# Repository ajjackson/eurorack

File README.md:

# ajjackson's DIY synth stuff

Somewhere to capture and develop some ideas for novel synthesiser
modules. Currently that means Eurorack, so +/- 12V power, TS mini
jacks, 10V peak-to-peak audio signals.

Not clear at this stage if the end goal is perfboard or PCBs, will see
how ambitious the designs get...

License is CC-by-sa where appropriate

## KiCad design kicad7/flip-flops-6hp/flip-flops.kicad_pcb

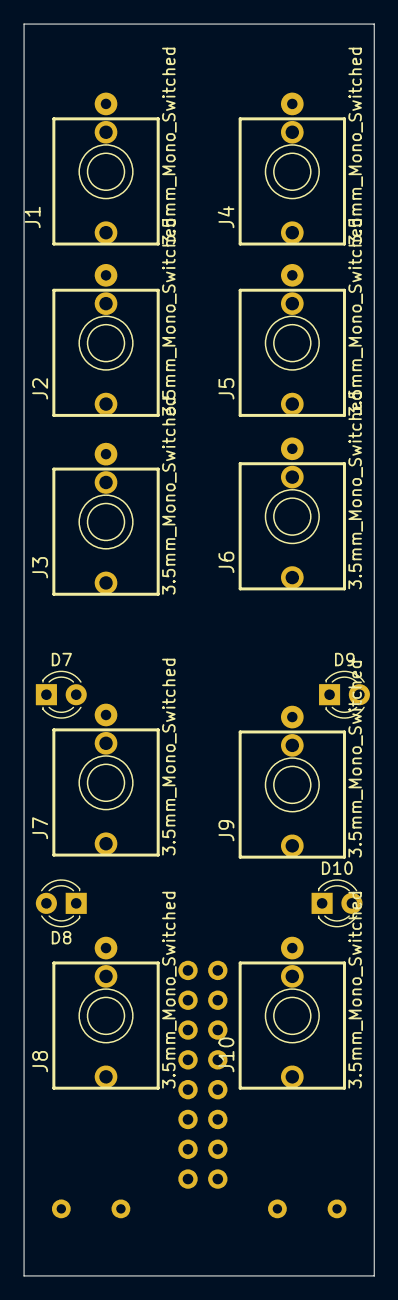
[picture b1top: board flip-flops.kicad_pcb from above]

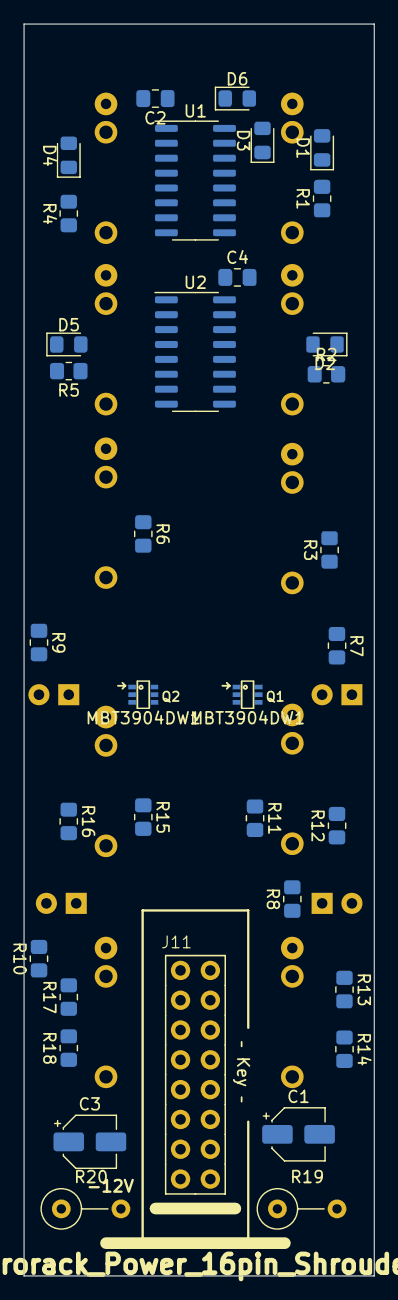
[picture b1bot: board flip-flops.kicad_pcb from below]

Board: 2 copper layers, 29.8 x 106.7 mm, 49 parts (35 on the bottom side), 39 nets, no tracks yet.

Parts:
C1, C3: 10uF_4x5.3_10V; CP_Elec_4x5.3
C2, C4: 100n; C_0805_2012Metric_Pad1.18x1.45mm_HandSolder
D1, D2, D3, D4, D5, D6: D_Schottky; D_0805_2012Metric_Pad1.15x1.40mm_HandSolder
D7, D8, D9, D10: LED; LED_D3.0mm_FlatTop
J1, J2, J3, J4, J5, J6, J7, J8, J9, J10: 3.5mm_Mono_Switched; EighthInch_PJ398SM
J11: Eurorack_Power_16pin_Shrouded; Pins_2x08_2.54mm_TH_EuroPower_Shrouded
Q1, Q2: MBT3904DW1; SOT-363_SC-70-6
R1, R2, R3, R4, R5, R6: 100k; R_0805_2012Metric_Pad1.20x1.40mm_HandSolder
R7, R8, R9, R10, R11, R12, R13, R14, R15, R16, R17, R18: 2.2k; R_0805_2012Metric_Pad1.20x1.40mm_HandSolder
R19, R20: 10R; R_Axial_DIN0309_L9.0mm_D3.2mm_P5.08mm_Vertical
U1: 4050; SOIC-16_3.9x9.9mm_P1.27mm
U2: 4013; SOIC-16_3.9x9.9mm_P1.27mm

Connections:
+5V: C2.1, C3.1, C4.1, R20.2, U1.1 (VCC), U2.14 (VDD)
+12V: C1.1, Q1.3 (C2), Q1.6 (C1), Q2.3 (C2), Q2.6 (C1), R19.1
/INV_OUT_1: J1.3 (SW), J8.1 (SIG), R13.2, R14.1
/INV_OUT_2: J4.3 (SW), J10.1 (SIG), R17.2, R18.1
GND: C1.2, C2.2, C3.2, C4.2, D1.2 (A), D2.2 (A), D3.2 (A), D4.2 (A), D5.2 (A), D6.2 (A), D7.1 (K), D8.1 (K), D9.1 (K), D10.1 (K), J1.2 (SHEILD), J2.2 (SHEILD), J3.2 (SHEILD), J3.3 (SW), J4.2 (SHEILD), J5.2 (SHEILD), J6.2 (SHEILD), J7.2 (SHEILD), J8.2 (SHEILD), J9.2 (SHEILD), J10.2 (SHEILD), J11.9 (GND), J11.10 (GND), J11.11 (GND), J11.12 (GND), J11.13 (-12), J11.14 (-12V), R12.2, R14.2, R16.2, R18.2, U1.8 (VSS), U2.7 (VSS)
unnamed: D1.1 (K), R1.2, U1.9
unnamed: D2.1 (K), R2.2, U1.11
unnamed: D3.1 (K), R3.2, U1.14
unnamed: D4.1 (K), R4.2, U1.3
unnamed: D5.1 (K), R5.2, U1.5
unnamed: D6.1 (K), R6.2, U1.7
unnamed: D7.2 (A), R7.2
unnamed: D8.2 (A), R8.2
unnamed: D9.2 (A), R9.2
unnamed: D10.2 (A), R10.2
unnamed: J1.1 (SIG), R1.1
unnamed: J2.1 (SIG), R2.1
unnamed: J3.1 (SIG), R3.1
unnamed: J4.1 (SIG), R4.1
unnamed: J5.1 (SIG), R5.1
unnamed: J6.1 (SIG), R6.1
unnamed: J7.1 (SIG), R11.2, R12.1
unnamed: J9.1 (SIG), R15.2, R16.1
unnamed: J11.7 (12V), J11.8 (+12V), R19.2
unnamed: J11.5 (+12V), J11.6, R20.1
unnamed: Q1.2 (B1), U2.13 (Q)
unnamed: Q1.1 (E1), R7.1, R11.1
unnamed: Q1.5 (B2), U2.12 (~Q)
unnamed: Q1.4 (E2), R8.1, R13.1
unnamed: Q2.2 (B1), U2.1 (Q)
unnamed: Q2.1 (E1), R9.1, R15.1
unnamed: Q2.5 (B2), U2.2 (~Q)
unnamed: Q2.4 (E2), R10.1, R17.1
unnamed: U1.4, U2.3 (C)
unnamed: U1.2, U2.5 (D)
unnamed: U1.6, U2.4 (R)
unnamed: U1.12, U2.11 (C)
unnamed: U1.10, U2.9 (D)
unnamed: U1.15, U2.10 (R)

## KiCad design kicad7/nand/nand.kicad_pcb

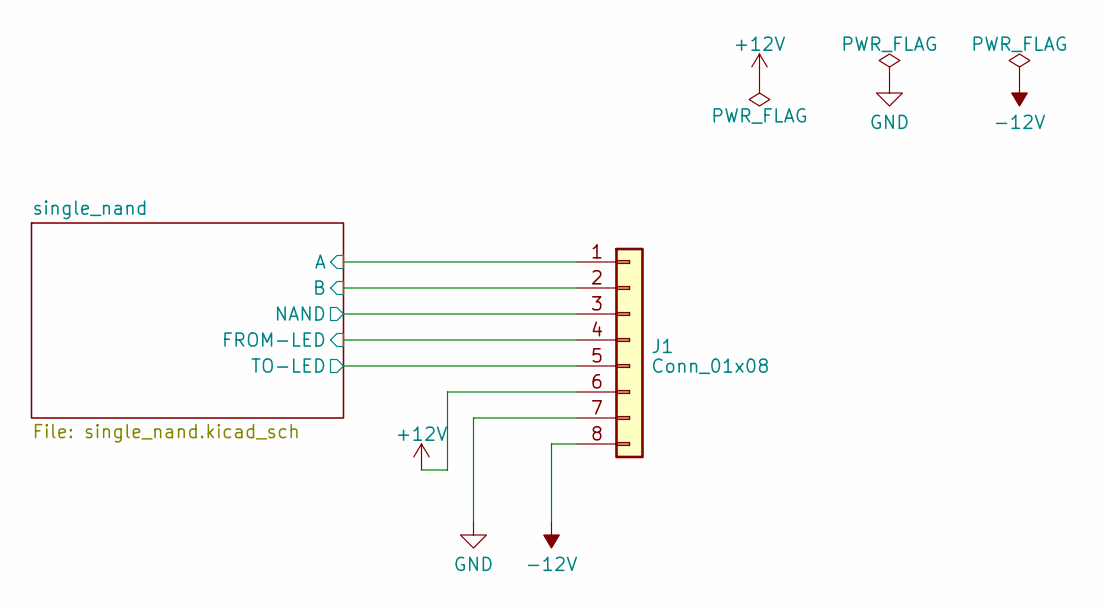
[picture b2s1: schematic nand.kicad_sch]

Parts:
J1: Conn_01x08; PinHeader_1x08_P2.54mm_Horizontal

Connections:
+12V: J1.6; also elsewhere on the board
-12V: J1.8; also elsewhere on the board
/single_nand/A: J1.1; also elsewhere on the board
/single_nand/B: J1.2; also elsewhere on the board
/single_nand/FROM-LED: J1.4; also elsewhere on the board
/single_nand/NAND: J1.3; also elsewhere on the board
/single_nand/TO-LED: J1.5; also elsewhere on the board
GND: J1.7; also elsewhere on the board

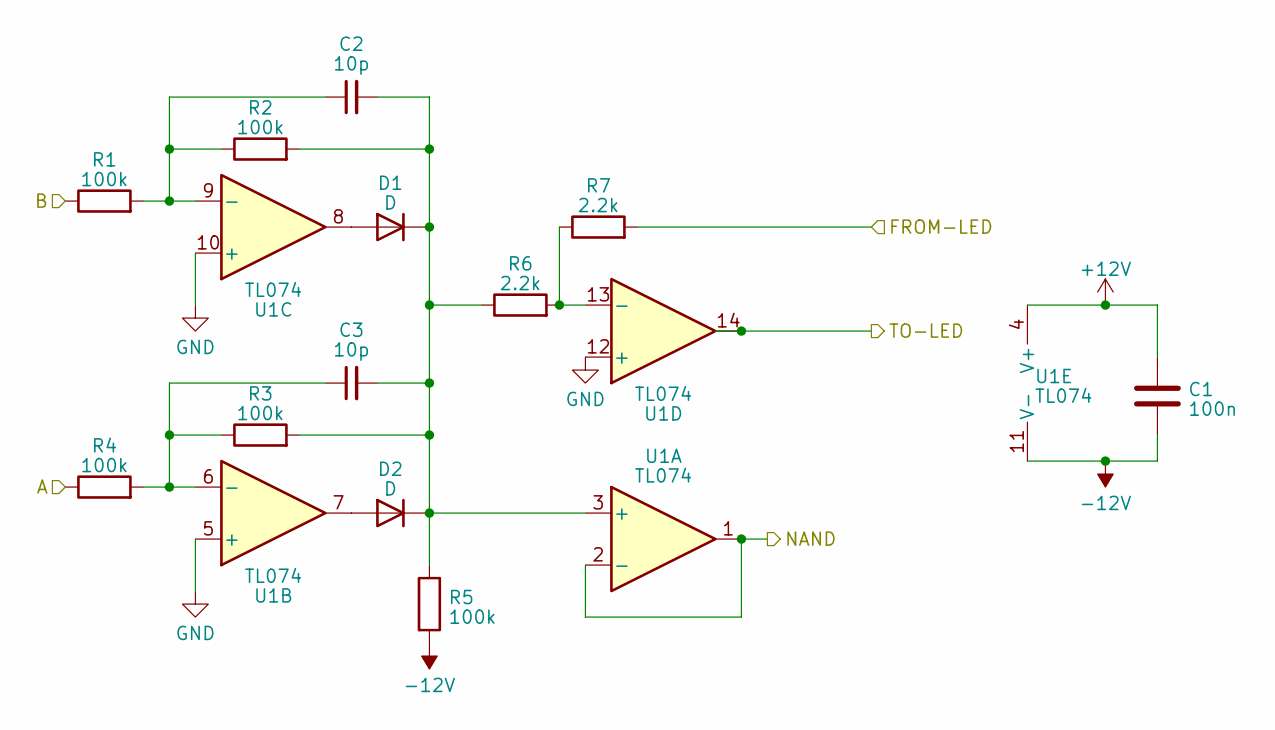
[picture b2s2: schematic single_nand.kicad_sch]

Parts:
C1: 100n; C_Disc_D5.0mm_W2.5mm_P5.00mm
C2, C3: 10p; C_Disc_D5.0mm_W2.5mm_P5.00mm
D1, D2: D; D_DO-34_SOD68_P7.62mm_Horizontal
R1, R2, R3, R4, R5: 100k; R_Axial_DIN0207_L6.3mm_D2.5mm_P7.62mm_Horizontal
R6, R7: 2.2k; R_Axial_DIN0207_L6.3mm_D2.5mm_P7.62mm_Horizontal
U1: TL074; DIP-14_W7.62mm

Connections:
+12V: C1.1, U1.4 (V+); also elsewhere on the board
-12V: C1.2, R5.2, U1.11 (V-); also elsewhere on the board
/single_nand/A: R1.1; also elsewhere on the board
/single_nand/B: R4.1; also elsewhere on the board
/single_nand/FROM-LED: R7.2; also elsewhere on the board
/single_nand/NAND: U1.1, U1.2 (-); also elsewhere on the board
/single_nand/TO-LED: U1.14; also elsewhere on the board
GND: U1.5 (+), U1.10 (+), U1.12 (+); also elsewhere on the board
unnamed: D1.2 (A), U1.8
unnamed: C2.2, C3.2, D1.1 (K), D2.1 (K), R2.2, R3.2, R5.1, R6.1, U1.3 (+)
unnamed: D2.2 (A), U1.7
unnamed: C3.1, R3.1, R4.2, U1.6 (-)
unnamed: C2.1, R1.2, R2.1, U1.9 (-)
unnamed: R6.2, R7.1, U1.13 (-)

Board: 2 copper layers, 14 parts (0 on the bottom side), 14 nets, no tracks yet.

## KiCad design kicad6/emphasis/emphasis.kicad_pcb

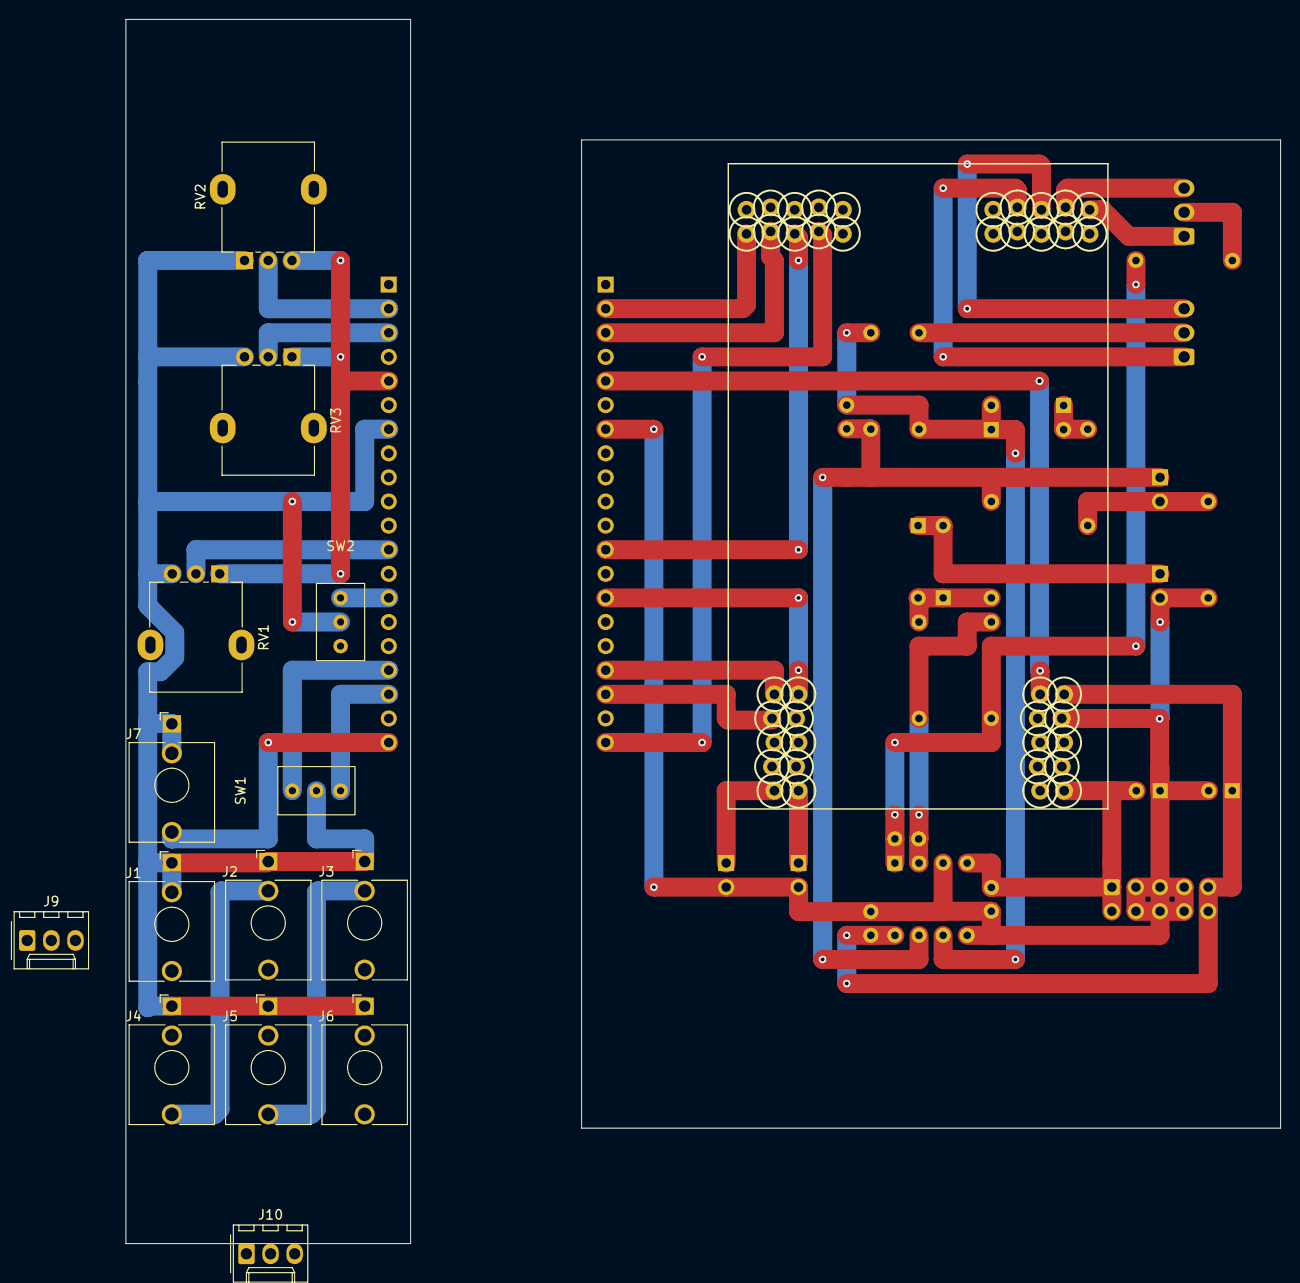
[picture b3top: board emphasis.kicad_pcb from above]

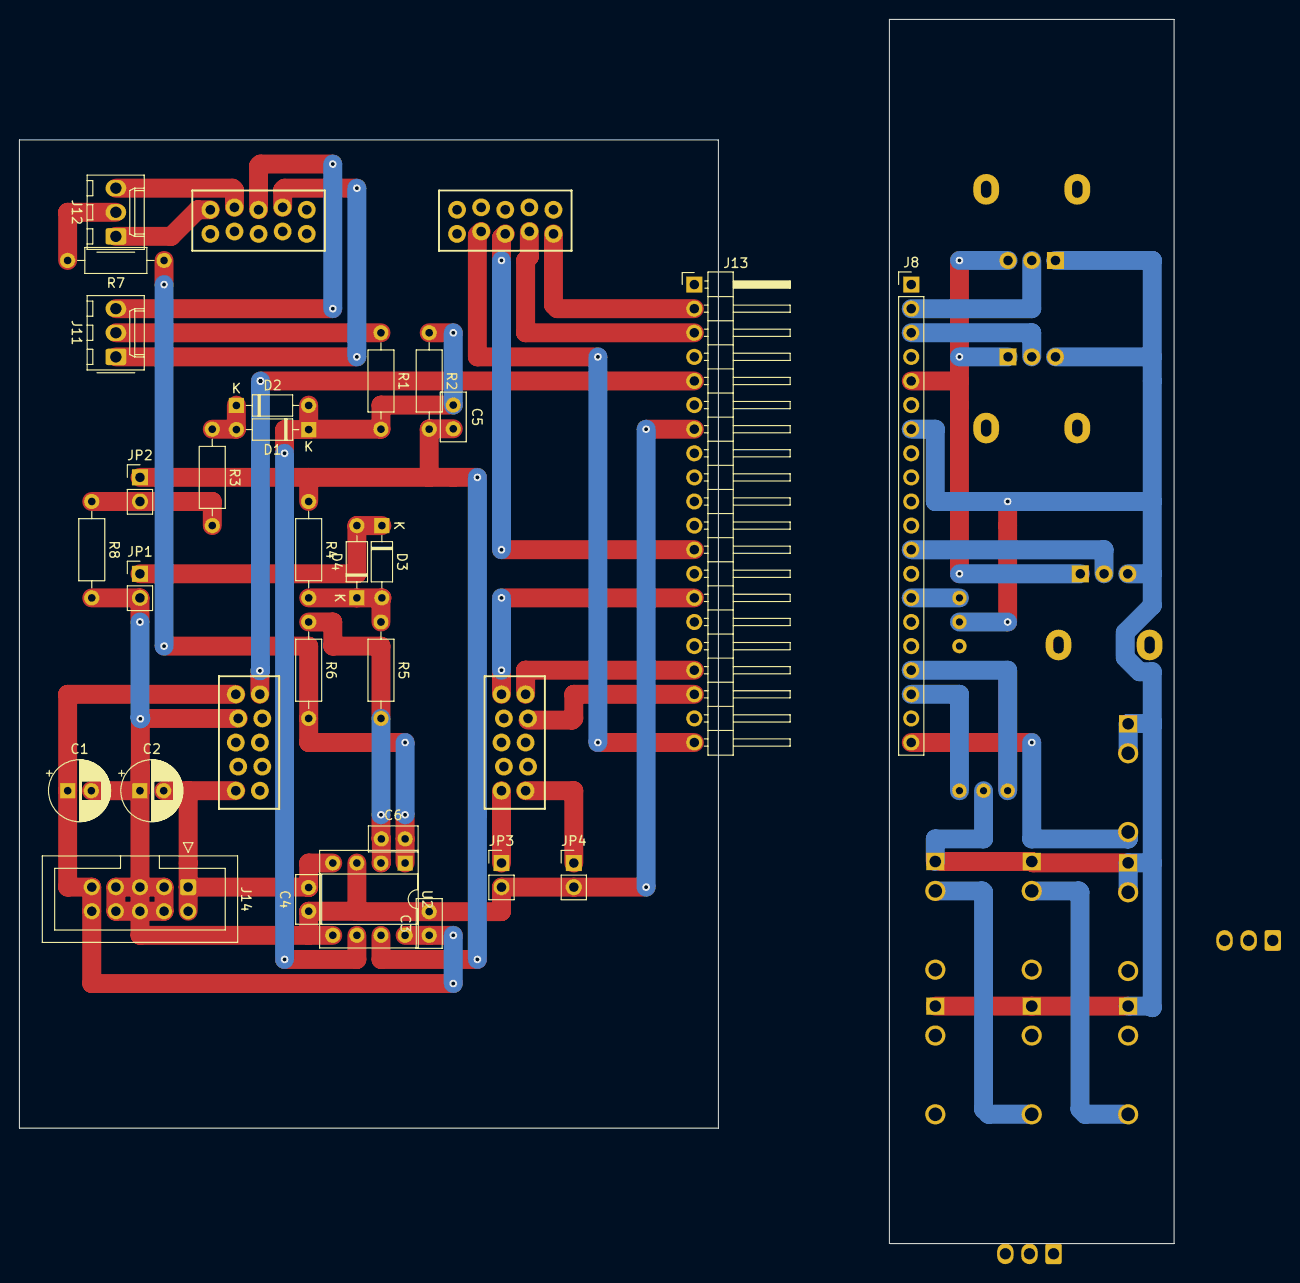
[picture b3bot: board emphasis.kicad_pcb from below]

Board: 2 copper layers, 121.7 x 129.0 mm, 43 parts (28 on the bottom side), 36 nets.

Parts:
C1, C2: 10uF; CP_Radial_D6.3mm_P2.50mm
C3, C4: 100nF; C_Disc_D5.0mm_W2.5mm_P2.50mm
C5, C6: 10pF; C_Disc_D5.0mm_W2.5mm_P2.50mm
D1, D2, D3, D4: 1N4148; D_DO-35_SOD27_P7.62mm_Horizontal
J1: EMPH_IN; Jack_3.5mm_QingPu_WQP-PJ398SM_Vertical_CircularHoles
J2: DIST_IN; Jack_3.5mm_QingPu_WQP-PJ398SM_Vertical_CircularHoles
J3: DE_EMPH_IN; Jack_3.5mm_QingPu_WQP-PJ398SM_Vertical_CircularHoles
J4: EMPH_OUT; Jack_3.5mm_QingPu_WQP-PJ398SM_Vertical_CircularHoles
J5: DIST_OUT; Jack_3.5mm_QingPu_WQP-PJ398SM_Vertical_CircularHoles
J6: DE_EMPH_OUT; Jack_3.5mm_QingPu_WQP-PJ398SM_Vertical_CircularHoles
J7: AudioJack2_SwitchT; Jack_3.5mm_QingPu_WQP-PJ398SM_Vertical_CircularHoles
J8: Conn_01x20_Female; PinHeader_1x20_P2.54mm_Vertical
J9, J10: Conn_01x03_Female; Molex_KK-254_AE-6410-03A_1x03_P2.54mm_Vertical
J11, J12: Conn_01x03_Male; Molex_KK-254_AE-6410-03A_1x03_P2.54mm_Vertical
J13: Conn_01x20_Male; PinHeader_1x20_P2.54mm_Horizontal
J14: Conn_02x05; IDC-Header_2x05_P2.54mm_Vertical
JP1, JP2, JP3, JP4: Jumper_2_Bridged; PinHeader_1x02_P2.54mm_Vertical
R1: 100k; R_Axial_DIN0207_L6.3mm_D2.5mm_P10.16mm_Horizontal
R2, R6: 47k; R_Axial_DIN0207_L6.3mm_D2.5mm_P10.16mm_Horizontal
R3: 10k; R_Axial_DIN0207_L6.3mm_D2.5mm_P10.16mm_Horizontal
R4: 2.2k; R_Axial_DIN0207_L6.3mm_D2.5mm_P10.16mm_Horizontal
R5: 4.7k; R_Axial_DIN0207_L6.3mm_D2.5mm_P10.16mm_Horizontal
R7: 1k; R_Axial_DIN0207_L6.3mm_D2.5mm_P10.16mm_Horizontal
R8: 22k; R_Axial_DIN0207_L6.3mm_D2.5mm_P10.16mm_Horizontal
RV1, RV2, RV3: R_Potentiometer; Potentiometer_Alpha_RD901F-40-00D_Single_Vertical
SW1: SW_SPDT_MSM; Dailywell sub-miniature toggle switch
SW2: SW_SPDT; Dailywell sub-miniature toggle switch
U1: ES_DAISY_PATCH_SM_REV1-Electrosmith-Boards; ES_DAISY_PATCH_SM_REV1
U2: TL072; DIP-8_W7.62mm_Socket

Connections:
+5V: J8.5, J13.5, RV1.1, RV2.3, RV3.1, U1.A6 (+5V)
+12V: C1.1, C3.1, J14.9, J14.10, U1.A5 (+12V), U2.8 (V+)
-12V: C2.2, C4.2, J14.1, J14.2, U1.A1 (-12V), U2.4 (V-)
/CV_DEST: J13.14, U1.D5 (SDMMC_D0)
/CV_JACK: J7.T, J8.20, J13.20, U1.C9 (CV8)
/CV_POT: J8.12, J13.12, RV1.2, U1.C8 (CV7)
/DE_EMPH_IN: J11.3, U1.B3 (AUDIO_IN_R)
/DE_EMPH_OUT: J12.1, U1.B1 (AUDIO_OUT_R)
/EMPH_IN: J11.1, U1.B4 (AUDIO_IN_L)
/EMPH_OUT: J12.3, U1.B2 (AUDIO_OUT_L)
/EMPH_POT: J8.3, J13.3, RV3.2, U1.C7 (CV6)
/FREQ_POT: J8.2, J13.2, RV2.2, U1.C6 (CV5)
/LED_clipper/Clipper_in: J11.2, R1.1
/LED_clipper/Clipper_out: J12.2, R7.2
/LED_clipper/SC_jumper_in: C5.2, JP2.1 (A), R2.2, R4.1, U2.7
/LED_clipper/SC_jumper_out: JP2.2 (B), R3.2, R8.1
/LED_clipper/hard_clipping_sink: D3.1 (K), D4.2 (A), JP1.1 (A)
/SHELF_1: J13.18, U1.D7 (SDMMC_CMD)
/SHELF_2: J13.17, U1.D6 (SDMMC_CK)
GND: C1.2, C2.1, C3.2, C4.1, J1.S, J1.TN, J2.S, J3.S, J4.S, J5.S, J6.S, J7.S, J7.TN, J8.7, J13.7, J14.3, J14.4, J14.5, J14.6, J14.7, J14.8, JP1.2 (B), JP3.2 (B), JP4.2 (B), R8.2, RV1.3, RV2.1, RV3.3, SW1.2, SW2.2 (B), U1.A4 (GND), U2.3 (+), U2.5 (+)
unnamed: C5.1, D1.1 (K), D2.2 (A), R1.2, R2.1, U2.6 (-)
unnamed: C6.1, R5.2, R6.1, U2.2 (-)
unnamed: C6.2, R6.2, R7.1, U2.1
unnamed: D1.2 (A), D2.1 (K), R3.1
unnamed: D3.2 (A), D4.1 (K), R4.2, R5.1
unnamed: J1.T, J9.1
unnamed: J2.T, J9.2
unnamed: J3.T, J9.3
unnamed: J8.14, SW2.1 (A)
unnamed: J8.17, SW1.1
unnamed: J8.18, SW1.3
unnamed: J2.TN, J4.T, J10.1
unnamed: J3.TN, J5.T, J10.2
unnamed: J6.T, J10.3
unnamed: JP3.1 (A), U1.D1 (SPI_NSS)
unnamed: JP4.1 (A), U1.D10 (SPI_SCK)

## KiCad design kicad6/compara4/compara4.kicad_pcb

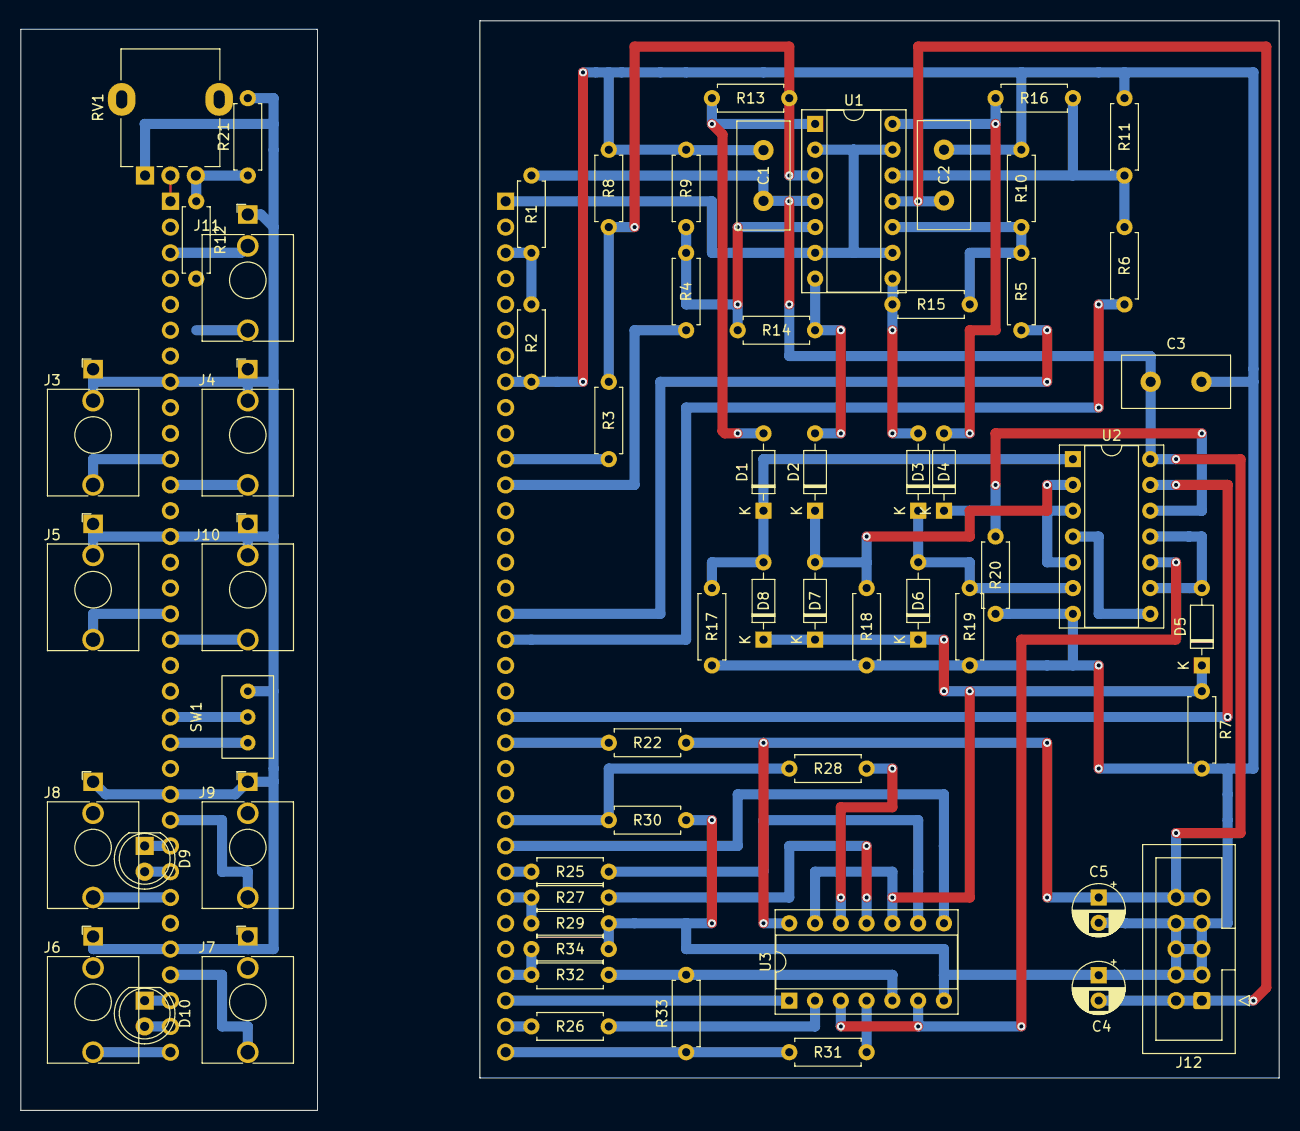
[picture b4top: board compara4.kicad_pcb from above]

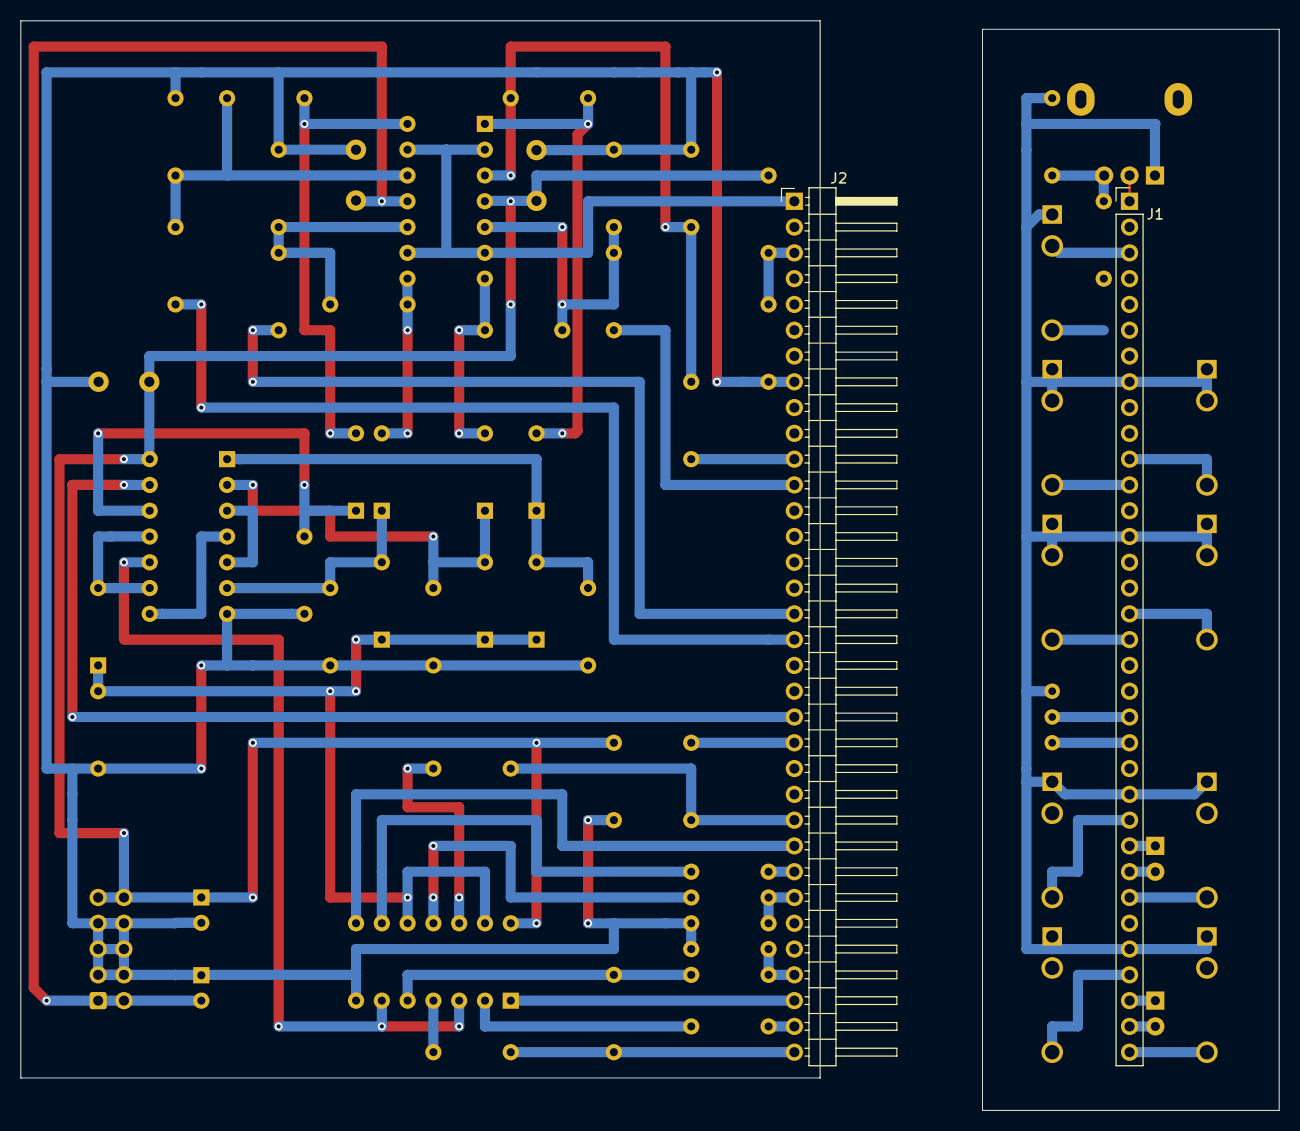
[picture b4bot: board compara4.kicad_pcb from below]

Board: 2 copper layers, 124.0 x 107.3 mm, 64 parts (2 on the bottom side), 60 nets.

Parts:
C1, C2, C3: 100n; C_Disc_D10.5mm_W5.0mm_P5.00mm
C4, C5: 10uF; CP_Radial_D5.0mm_P2.50mm
D1, D2, D3, D4, D5, D6, D7, D8: 1N4148; D_DO-35_SOD27_P7.62mm_Horizontal
D9, D10: LED_Dual_Bidirectional; LED_D5.0mm
J1: Conn_01x34_Female; PinHeader_1x34_P2.54mm_Vertical
J2: Conn_01x34_Male; PinHeader_1x34_P2.54mm_Horizontal
J3: In_1; Jack_3.5mm_QingPu_WQP-PJ398SM_Vertical_CircularHoles
J4: In_2; Jack_3.5mm_QingPu_WQP-PJ398SM_Vertical_CircularHoles
J5: In_3; Jack_3.5mm_QingPu_WQP-PJ398SM_Vertical_CircularHoles
J6: Out_XOR; Jack_3.5mm_QingPu_WQP-PJ398SM_Vertical_CircularHoles
J7: Out_XNOR; Jack_3.5mm_QingPu_WQP-PJ398SM_Vertical_CircularHoles
J8: Out_OR; Jack_3.5mm_QingPu_WQP-PJ398SM_Vertical_CircularHoles
J9: Out_NOR; Jack_3.5mm_QingPu_WQP-PJ398SM_Vertical_CircularHoles
J10: In_4; Jack_3.5mm_QingPu_WQP-PJ398SM_Vertical_CircularHoles
J11: CV_Jack; Jack_3.5mm_QingPu_WQP-PJ398SM_Vertical_CircularHoles
J12: Conn_02x05_Top_Bottom; IDC-Header_2x05_P2.54mm_Vertical
R1, R22: 10k; R_Axial_DIN0207_L6.3mm_D2.5mm_P7.62mm_Horizontal
R2, R7, R17, R18, R19, R20, R21: 100k; R_Axial_DIN0207_L6.3mm_D2.5mm_P7.62mm_Horizontal
R3, R4, R5, R6, R8, R9, R10, R11, R12: 47k; R_Axial_DIN0207_L6.3mm_D2.5mm_P7.62mm_Horizontal
R13, R14, R15, R16: 1M; R_Axial_DIN0207_L6.3mm_D2.5mm_P7.62mm_Horizontal
R25, R26, R27, R28, R29, R30, R31, R32, R33, R34: 2.2k; R_Axial_DIN0207_L6.3mm_D2.5mm_P7.62mm_Horizontal
RV1: 100k; Potentiometer_Alpha_RD901F-40-00D_Single_Vertical
SW1: SW_SPDT; Dailywell sub-miniature toggle switch
U1: TL074; DIP-14_W7.62mm_Socket
U2: 4070; DIP-14_W7.62mm_Socket
U3: 4041; DIP-14_W7.62mm_Socket

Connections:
+12V: C1.1, C3.1, C5.1, J12.9, J12.10, R1.2, R22.1, U1.4 (V+), U2.14 (VDD), U3.14 (Vdd)
-12V: C2.2, C4.2, J12.1, J12.2, U1.11 (V-)
/LED_OR_+: J2.26, U3.8
/LED_OR_-: J2.27, R25.1
/LED_XOR_+: J2.32, U3.1
/LED_XOR_-: J2.33, R26.1
/NOR: J2.25, R28.1, R30.1
/OR: J2.28, R27.1, R29.1
/Switch: J2.21, U2.13
/Threshold: J2.1, U1.2 (-), U1.6 (-), U1.9 (-), U1.13 (-)
/XNOR: J2.31, R32.1, R34.1
/XOR: J2.34, R31.1, R33.1
/controls/+12V: J1.22, SW1.1 (A)
/controls/Default_thresh: J1.3, J11.TN
/controls/IN1: J1.11, J3.T
/controls/IN2: J1.12, J4.T
/controls/IN3: J1.17, J5.T
/controls/IN4: J1.18, J10.T
/controls/LED_OR_+: D9.1 (KA), J1.26
/controls/LED_OR_-: D9.2 (AK), J1.27
/controls/LED_XOR_+: D10.1 (KA), J1.32
/controls/LED_XOR_-: D10.2 (AK), J1.33
/controls/NOR: J1.25, J9.T
/controls/OR: J1.28, J8.T
/controls/Switch: J1.21, SW1.2 (B)
/controls/Threshold: J1.1, RV1.2
/controls/XNOR: J1.31, J7.T
/controls/XOR: J1.34, J6.T
GND: C1.2, C2.1, C3.2, C4.1, C5.2, J1.8, J1.14, J1.24, J1.30, J2.8, J3.S, J3.TN, J4.S, J4.TN, J5.S, J5.TN, J6.S, J7.S, J8.S, J9.S, J10.S, J10.TN, J11.S, J12.3, J12.4, J12.5, J12.6, J12.7, J12.8, R2.1, R7.2, R8.2, R9.2, R10.2, R11.2, R17.1, R18.1, R19.1, R20.1, R21.2, R29.2, R30.2, R33.2, R34.2, RV1.1, SW1.3 (C), U2.7 (VSS), U3.7 (Vss)
unnamed: D1.1 (K), D8.2 (A), R17.2, U2.1
unnamed: D1.2 (A), R13.2, U1.1
unnamed: D2.1 (K), D7.2 (A), R18.2, U2.2
unnamed: D2.2 (A), R14.2, U1.7
unnamed: D3.1 (K), D6.2 (A), R19.2, U2.6
unnamed: D3.2 (A), R15.2, U1.8
unnamed: D4.1 (K), R20.2, U2.12
unnamed: D4.2 (A), R16.2, U1.14
unnamed: D5.1 (K), D6.1 (K), D7.1 (K), D8.1 (K), R7.1, U3.10, U3.13
unnamed: D5.2 (A), U2.9, U2.11
unnamed: J2.3, R1.1, R2.2
unnamed: J2.11, R3.2
unnamed: J2.12, R4.2
unnamed: J2.17, R5.2
unnamed: J2.18, R6.2
unnamed: J2.22, R22.2
unnamed: J11.T, R12.2
unnamed: R5.1, R10.1, R15.1, U1.10 (+)
unnamed: R6.1, R11.1, R16.1, U1.12 (+)
unnamed: R12.1, R21.1, RV1.3
unnamed: R3.1, R8.1, R13.1, U1.3 (+)
unnamed: R4.1, R9.1, R14.1, U1.5 (+)
unnamed: R25.2, U3.9
unnamed: R26.2, U3.2
unnamed: R27.2, U3.11
unnamed: R28.2, U3.12
unnamed: R31.2, U3.4
unnamed: R32.2, U3.5
unnamed: U2.3, U2.5
unnamed: U2.4, U2.8
unnamed: U2.10, U3.3, U3.6

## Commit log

2021-08-27 Initialise repo with some notes
2021-08-31 More thoughts and simple crossover model
2021-09-01 ultrasonic pwm thoughts
2021-09-11 notes update
2021-09-11 common-mode note
2021-09-25 holiday updates
2021-09-25 Clipping chain: concept coming together
2021-10-11 Thoughts on serge-like folders
2021-10-15 PM Oscillator proposal
2021-10-15 misc notes
2021-10-15 opamp-based triangle tripling wavefolder: circuitjs demo
2021-10-15 Harmonics shaper - split from VCO?
2021-11-21 PWM ideas
2022-02-18 Holiday stuff: more notes and compara4 kicad6
2022-03-24 notes, some design bits, state of progress
2022-04-03 Remove transistors from Compara4 schematic
    - CD4041 can drive 500 mW total Each LED through 2.2V is about 65 mW
    - With potential divider to reduce output voltage, the power numbers for shorts get less scary than through 1k directly.
    - If gate output is shorted to ground through 2.2k resistor, it's effectively just another LED - no problem.
    - In a worst-case short to -12V, 130mW are drawn from CD4041. This would push it hard but probably not burn it out quickly.
    - The resistor between CD4041 and output "sees" twice the voltage drop and passes >1/4W. If this (or an additional low-value series resistor) is specified as a 1/8W then it could act as an additional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
    - Probably unne
2022-04-14 compara4; breakout controls, layout for perfboard
2022-04-14 looks like this extra pro file is trash?
2022-04-15 Add mixing section to first draft of polyshaper, add to repo
    This was migrated from kicad 5 to 6, let's hope there aren't any
    issues there...
2022-04-17 compara4 routing corrections: 2.54mm grid
2022-04-17 compara4: reverse pot and cleanup ERC
2022-04-18 compara4; alignment corrections, some jumper cleanup
2022-05-01 compara4 layout tweaks
2022-05-01 add Compara4 schematic pdf
2022-05-27 Emphasis initial layout
2022-05-29 emphasis pin shuffling
2022-05-30 Emphasis: flipped board, take 1
    Not entirely happy with the way this is going, might start again.
    Basically I messed up the orientation of the main board relative to
    the control board: to avoid having the patch_sm stick out the side,
    parts need to be mounted on the "back" of main board. But this flips
    the orientation of patch_sm and ICs, so everything needs to be
    re-routed.
2022-05-31 Emphasis take 3: flipped components, cleaner layout
2023-04-13 analog NAND take 1
2023-04-13 alt nand submodule layout. looking better but a lot of jumpers
2023-06-25 flip-flops 6hp
